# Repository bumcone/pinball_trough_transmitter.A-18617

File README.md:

# Pinball Trough Transmitter A-18617 / A-18617-1

-----
# WARNING

**WARNING:** I haven't done a run of these boards yet - they may not be right -
use at your own risk

# WARNING
-----

## Introduction

Pinball LED Trough Transmitter board ( like `5768-14121-02` PCB or `A-18617` /
`A-18617-1` when populated ).

## Supported Games

The following games used the `A-18617` / `A-18618-1` ( `5768-14121-02` PCB )
board:

|Game                       |Edition |Manufacturer  |
|:---                       |:---    |:---          |
|Attack from Mars           |        |Bally         |
|Cactus Canyon              |        |Bally         |
|Champion Pub               |        |Bally         |
|Cirqus Voltaire            |        |Bally         |
|Corvette                   |        |Bally         |
|Indy 500                   |        |Bally         |
|NBA Fastbreak              |        |Bally         |
|Revenge from Mars          |        |Bally         |
|Safe Cracker               |        |Bally         |
|Scared Stiff               |        |Bally         |
|Shadow                     |        |Bally         |
|Theatre of Magic           |        |Bally         |
|Who Dunnit                 |        |Bally         |
|World Cup Soccer           |        |Bally         |
|                           |        |              |
|Congo                      |        |Williams      |
|Dirty Harry                |        |Williams      |
|Flintstones                |        |Williams      |
|Jack Bot                   |        |Williams      |
|Johnny Mnemonic            |        |Williams      |
|Junkyard                   |        |Williams      |
|Medieval Madness           |        |Williams      |
|Monster Bash               |        |Williams      |
|No Fear                    |        |Williams      |
|No Good Gofers             |        |Williams      |
|Roadshow                   |        |Williams      |
|Star Wars Episode 1        |        |Williams      |
|Tales of the Arabian Nights|        |Williams      |
|                           |        |              |
|Attack from Mars (Remake)  |Classic |Chicago Gaming|
|Attack from Mars (Remake)  |Limited |Chicago Gaming|
|Attack from Mars (Remake)  |Special |Chicago Gaming|
|Monster Bash (Remake)      |Classic |Chicago Gaming|
|Monster Bash (Remake)      |Limited |Chicago Gaming|
|Monster Bash (Remake)      |Special |Chicago Gaming|

## LED Alignment

When mounted to a trough ( such as `A-16809-2` ), this board has its LEDs
aligned in the center of the pill shaped openings. This seems to be more like
the alignment of the `A-17982-AI` / `A-17982` board
( `5768-13660-01` PCB ) found in other Williams machines. This seems like a
better spot to put them and for my purpose (homebrew), it does not matter as I
will align the other board accordingly. If however, you were to use these boards
with an existing `A-18618` / `A-18618-1` you'd probably want the LEDs to align
at the bottom, in which case you'd use the
[bottom aligned](https://github.com/bumcone/pinball_trough_transmitter.A-18617/tree/bottom)
version of this board.

## Board design

----
[//]: # ( vim: set ts=4 sw=4 et cindent tw=80 ai si syn=markdown ft=markdown: )

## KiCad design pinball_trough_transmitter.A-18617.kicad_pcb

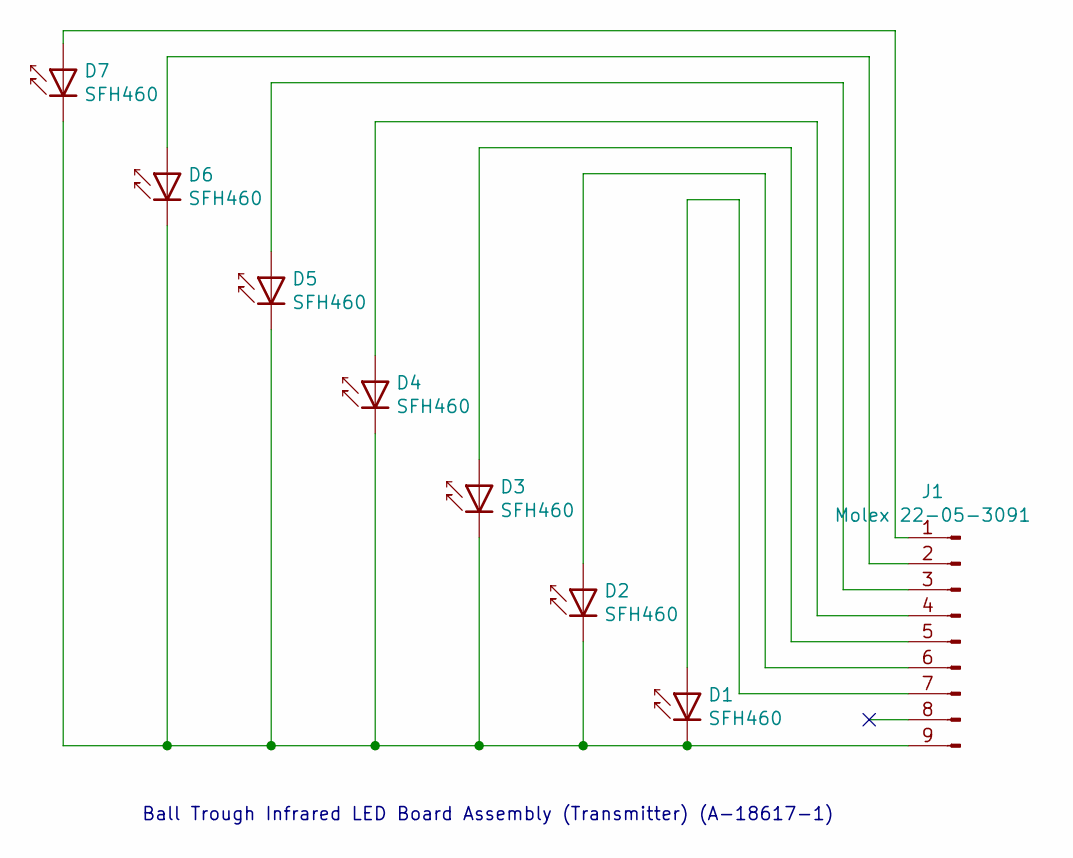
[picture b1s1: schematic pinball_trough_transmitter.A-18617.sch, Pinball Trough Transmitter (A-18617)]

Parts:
D1, D2, D3, D4, D5, D6, D7: SFH460; LED_D5.0mm_Clear
J1: Molex 22-05-3091; Molex_KK-254_AE-6410-09A_1x09_P2.54mm_Vertical

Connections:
unnamed: D1.1 (K), D2.1 (K), D3.1 (K), D4.1 (K), D5.1 (K), D6.1 (K), D7.1 (K), J1.9
unnamed: D1.2 (A), J1.7
unnamed: D2.2 (A), J1.6
unnamed: D3.2 (A), J1.5
unnamed: D4.2 (A), J1.4
unnamed: D5.2 (A), J1.3
unnamed: D6.2 (A), J1.2
unnamed: D7.2 (A), J1.1

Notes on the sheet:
Ball Trough Infrared LED Board Assembly (Transmitter) (A-18617-1)

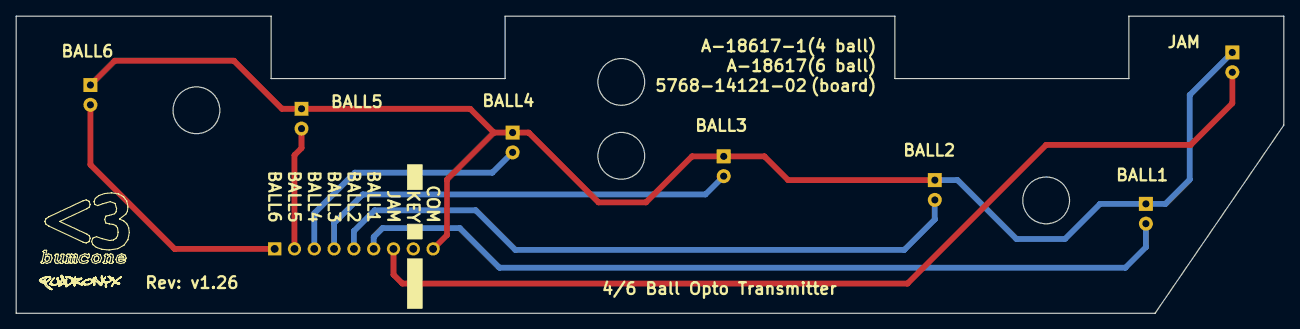
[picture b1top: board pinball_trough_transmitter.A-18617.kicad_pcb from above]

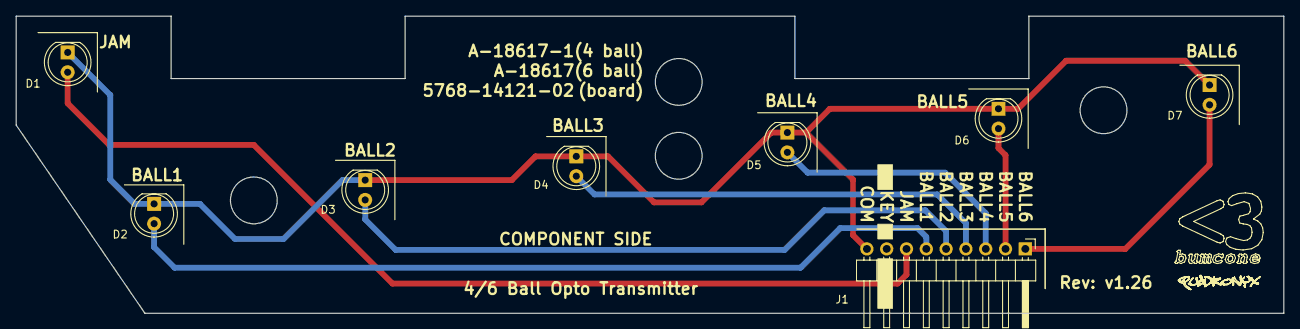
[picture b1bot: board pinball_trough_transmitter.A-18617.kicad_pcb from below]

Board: 2 copper layers, 162.6 x 38.1 mm, 8 parts (8 on the bottom side), 8 nets.

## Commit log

2021-09-16 Initial creation
2021-09-16 Minor adjustments
2022-09-16 Final adjustments (hopefully)
2022-09-16 Manually flip board
2022-09-16 Programmatically flip instead
2022-09-16 Almost there
2022-09-16 I think... we're done
2022-09-16 Add image
2022-09-16 Add warning
2022-09-20 Move screw holes
2022-09-20 More screw hole adjustment
2022-09-20 More center hole adjustments
2022-09-20 Front hole adjustment
2022-09-20 Remove lil' bumcone
2022-09-20 Test potential new position for JAM
2022-09-20 Move JAM LED
2022-09-20 Move J1 header back a little
2022-09-20 Update README and board image
2022-09-20 Use Molex connector
2022-09-20 Align LEDs with the center of the trough holes
2022-09-29 Minor board rearranging
